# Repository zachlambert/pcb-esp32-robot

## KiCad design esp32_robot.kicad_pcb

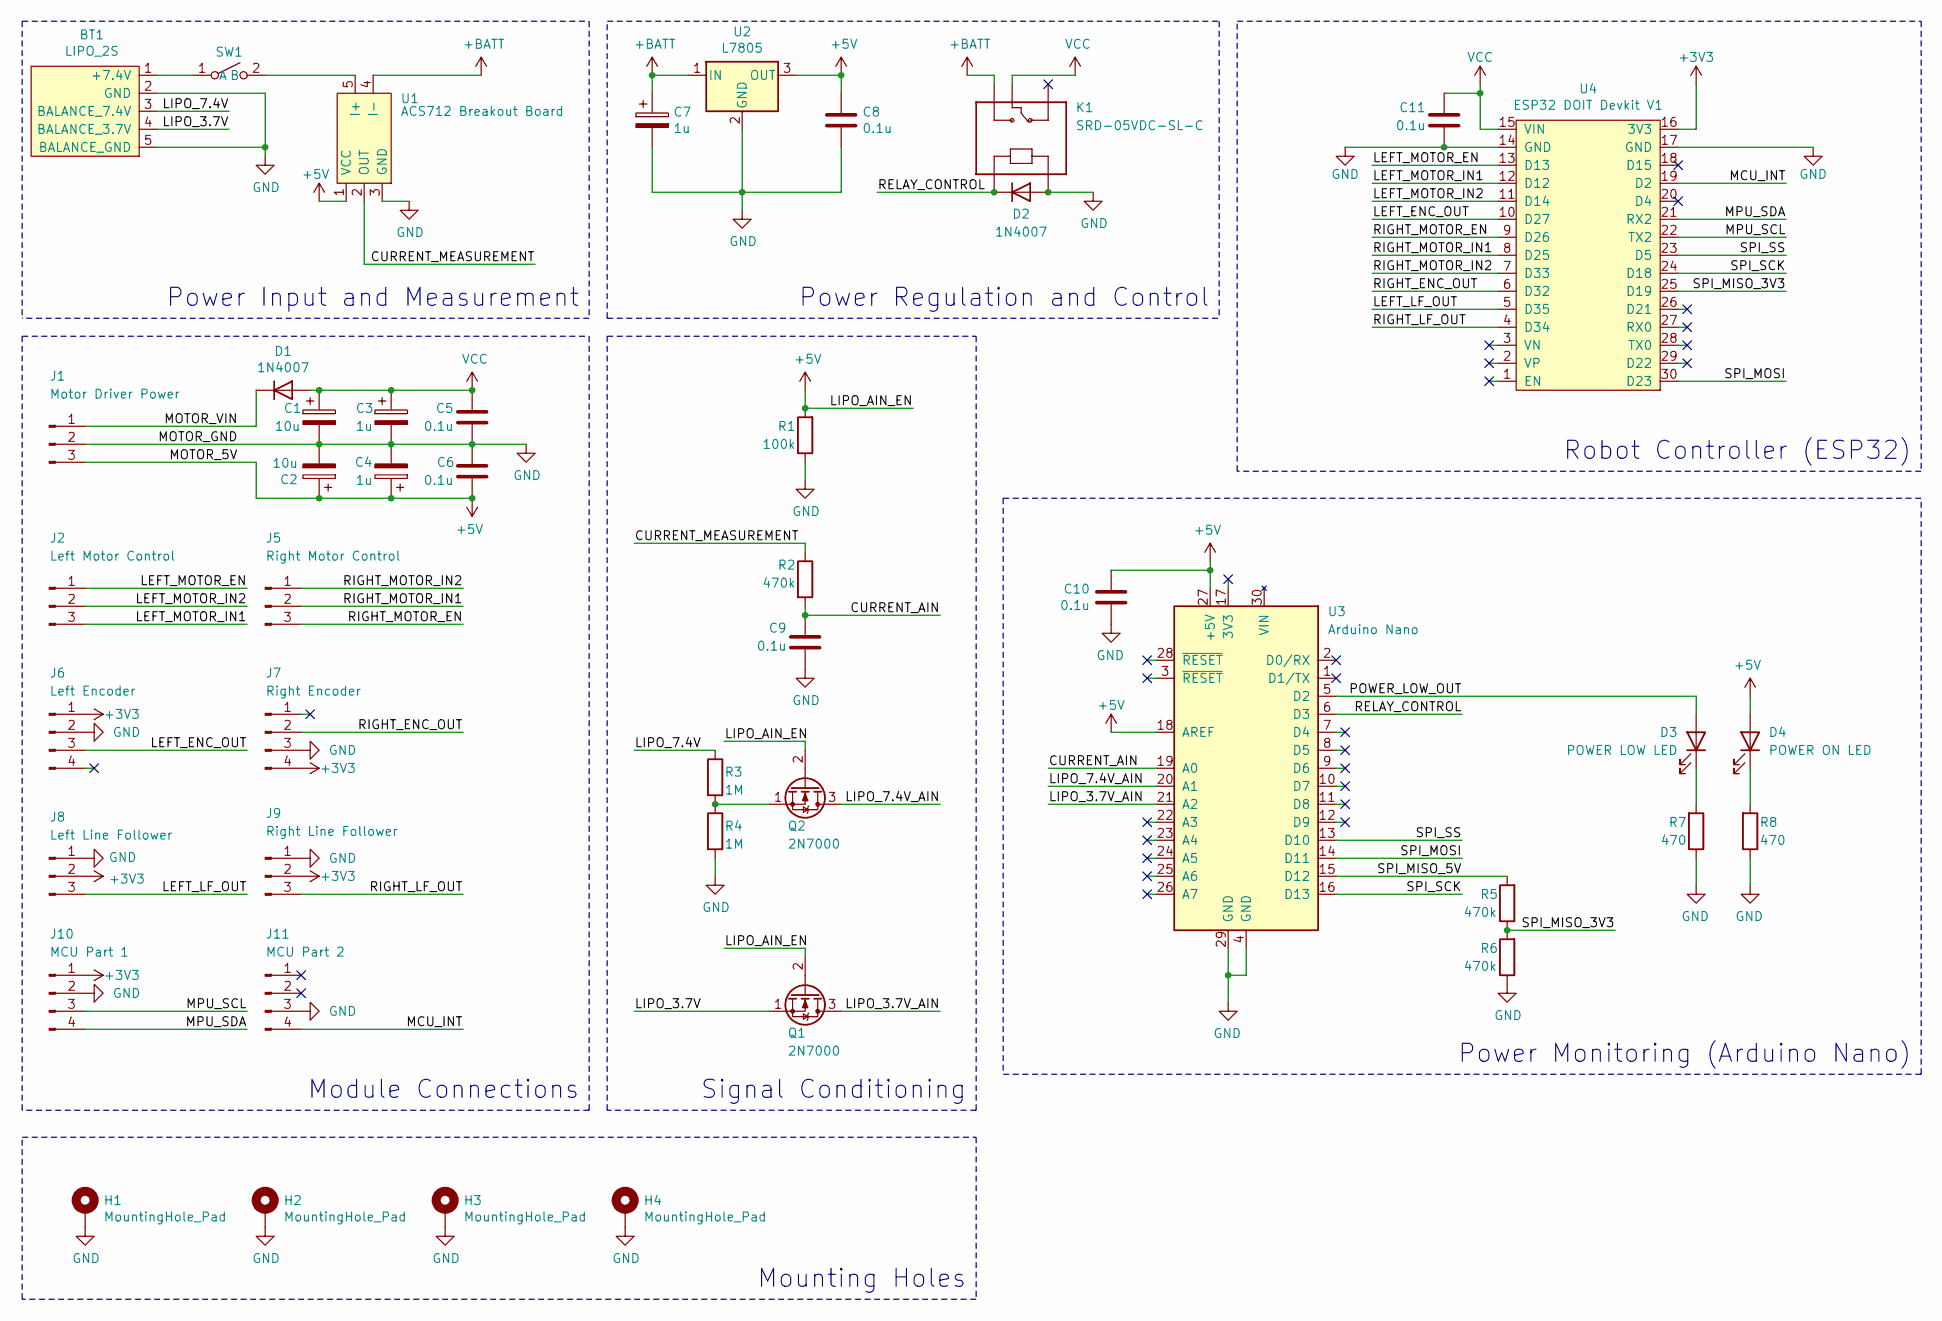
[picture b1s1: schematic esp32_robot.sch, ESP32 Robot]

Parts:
BT1: LIPO_2S
C1, C2: 10u; C_Radial_D5.0mm_H11.0mm_P2.00mm
C3, C4, C7: 1u; C_Radial_D5.0mm_H11.0mm_P2.00mm
C5, C6, C8, C9, C10, C11: 0.1u; C_Disc_D5.0mm_W2.5mm_P5.00mm
D1, D2: 1N4007; D_A-405_P7.62mm_Horizontal
D3: POWER LOW LED; LED_D5.0mm
D4: POWER ON LED; LED_D5.0mm
H1, H2, H3, H4: MountingHole_Pad; MountingHole_2.7mm_M2.5
J1: Motor Driver Power; JST_XH_B3B-XH-A_1x03_P2.50mm_Vertical
J2: Left Motor Control; JST_XH_B3B-XH-A_1x03_P2.50mm_Vertical
J5: Right Motor Control; JST_XH_B3B-XH-A_1x03_P2.50mm_Vertical
J6: Left Encoder; JST_XH_B4B-XH-A_1x04_P2.50mm_Vertical
J7: Right Encoder; JST_XH_B4B-XH-A_1x04_P2.50mm_Vertical
J8: Left Line Follower; JST_XH_B3B-XH-A_1x03_P2.50mm_Vertical
J9: Right Line Follower; JST_XH_B3B-XH-A_1x03_P2.50mm_Vertical
J10: MCU Part 1; JST_XH_B4B-XH-A_1x04_P2.50mm_Vertical
J11: MCU Part 2; JST_XH_B4B-XH-A_1x04_P2.50mm_Vertical
K1: SRD-05VDC-SL-C
Q1, Q2: 2N7000; TO-92_Inline
R1: 100k; R_Axial_DIN0207_L6.3mm_D2.5mm_P10.16mm_Horizontal
R2, R5, R6: 470k; R_Axial_DIN0207_L6.3mm_D2.5mm_P10.16mm_Horizontal
R3, R4: 1M; R_Axial_DIN0207_L6.3mm_D2.5mm_P10.16mm_Horizontal
R7, R8: 470; R_Axial_DIN0207_L6.3mm_D2.5mm_P10.16mm_Horizontal
SW1: power_switch; JST_XH_B2B-XH-A_1x02_P2.50mm_Vertical
U1: ACS712 Breakout Board; ACs712
U2: L7805; TO-220-3_Horizontal_TabDown
U3: Arduino Nano; Arduino_Nano
U4: ESP32 DOIT Devkit V1; DOIT-DEVKIT-V1

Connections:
+3V3: J6.1, J7.4, J8.2, J9.2, J10.1, U4.16 (3V3)
+5V: C2.1, C4.1, C6.2, C8.1, C10.1, D4.2 (A), J1.3, Q1.2 (G), Q2.2 (G), R1.2, U1.1 (VCC), U2.3 (OUT), U3.18 (AREF), U3.27 (+5V)
+BATT: C7.1, K1.NO, U1.4 (I-), U2.1 (IN)
/CURRENT_AIN: C9.1, R2.2, U3.19 (A0)
/CURRENT_MEASUREMENT: R2.1, U1.2 (OUT)
/LEFT_ENC_OUT: J6.3, U4.10 (D27)
/LEFT_LF_OUT: J8.3, U4.5 (D35)
/LEFT_MOTOR_EN: J2.1, U4.13 (D13)
/LEFT_MOTOR_IN1: J2.3, U4.12 (D12)
/LEFT_MOTOR_IN2: J2.2, U4.11 (D14)
/LIPO_3.7V: BT1.4 (BALANCE_3.7V), Q1.1 (S)
/LIPO_3.7V_AIN: Q1.3 (D), U3.21 (A2)
/LIPO_7.4V: BT1.3 (BALANCE_7.4V), R3.1
/LIPO_7.4V_AIN: Q2.3 (D), U3.20 (A1)
/MCU_INT: J11.4, U4.19 (D2)
/MOTOR_VIN: D1.1 (K), J1.1
/MPU_SCL: J10.3, U4.22 (TX2)
/MPU_SDA: J10.4, U4.21 (RX2)
/POWER_LOW_OUT: D3.2 (A), U3.5 (D2)
/RELAY_CONTROL: D2.1 (K), K1.A1, U3.6 (D3)
/RIGHT_ENC_OUT: J7.2, U4.6 (D32)
/RIGHT_LF_OUT: J9.3, U4.4 (D34)
/RIGHT_MOTOR_EN: J5.3, U4.9 (D26)
/RIGHT_MOTOR_IN1: J5.2, U4.8 (D25)
/RIGHT_MOTOR_IN2: J5.1, U4.7 (D33)
/SPI_MISO_3V3: R5.1, R6.2, U4.25 (D19)
/SPI_MISO_5V: R5.2, U3.15 (D12)
/SPI_MOSI: U3.14 (D11), U4.30 (D23)
/SPI_SCK: U3.16 (D13), U4.24 (D18)
/SPI_SS: U3.13 (D10), U4.23 (D5)
GND: BT1.2 (GND), BT1.5 (BALANCE_GND), C1.2, C2.2, C3.2, C4.2, C5.2, C6.1, C7.2, C8.2, C9.2, C10.2, C11.1, D2.2 (A), H1.1, H2.1, H3.1, H4.1, J1.2, J6.2, J7.3, J8.1, J9.1, J10.2, J11.3, K1.A2, R1.1, R4.2, R6.1, R7.1, R8.1, U1.3 (GND), U2.2 (GND), U3.4 (GND), U3.29 (GND), U4.14 (GND), U4.17 (GND)
unnamed: BT1.1 (+7.4V), SW1.1 (A)
unnamed: D3.1 (K), R7.2
unnamed: D4.1 (K), R8.2
unnamed: Q2.1 (S), R3.2, R4.1
unnamed: SW1.2 (B), U1.5 (I+)
VCC: C1.1, C3.1, C5.1, C11.2, D1.2 (A), K1.COM, U4.15 (VIN)

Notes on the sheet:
Power Input and Measurement
Module Connections
Power Regulation and Control
Signal Conditioning
Mounting Holes
Robot Controller (ESP32)
Power Monitoring (Arduino Nano)

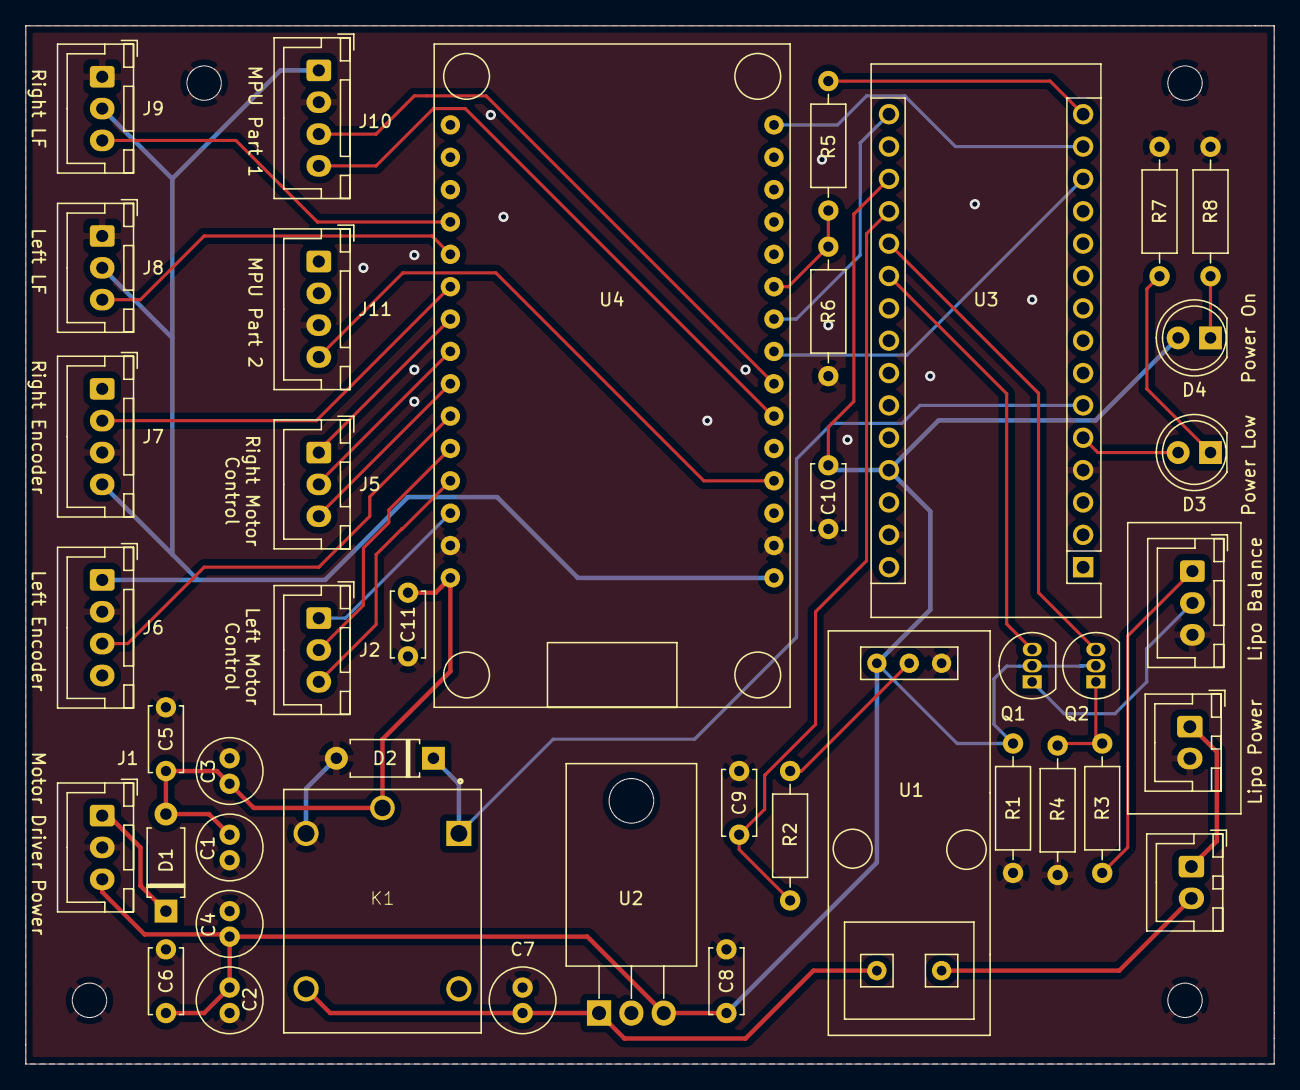
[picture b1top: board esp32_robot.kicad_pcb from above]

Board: 2 copper layers, 98.0 x 81.5 mm, 45 parts (0 on the bottom side), 37 nets.
